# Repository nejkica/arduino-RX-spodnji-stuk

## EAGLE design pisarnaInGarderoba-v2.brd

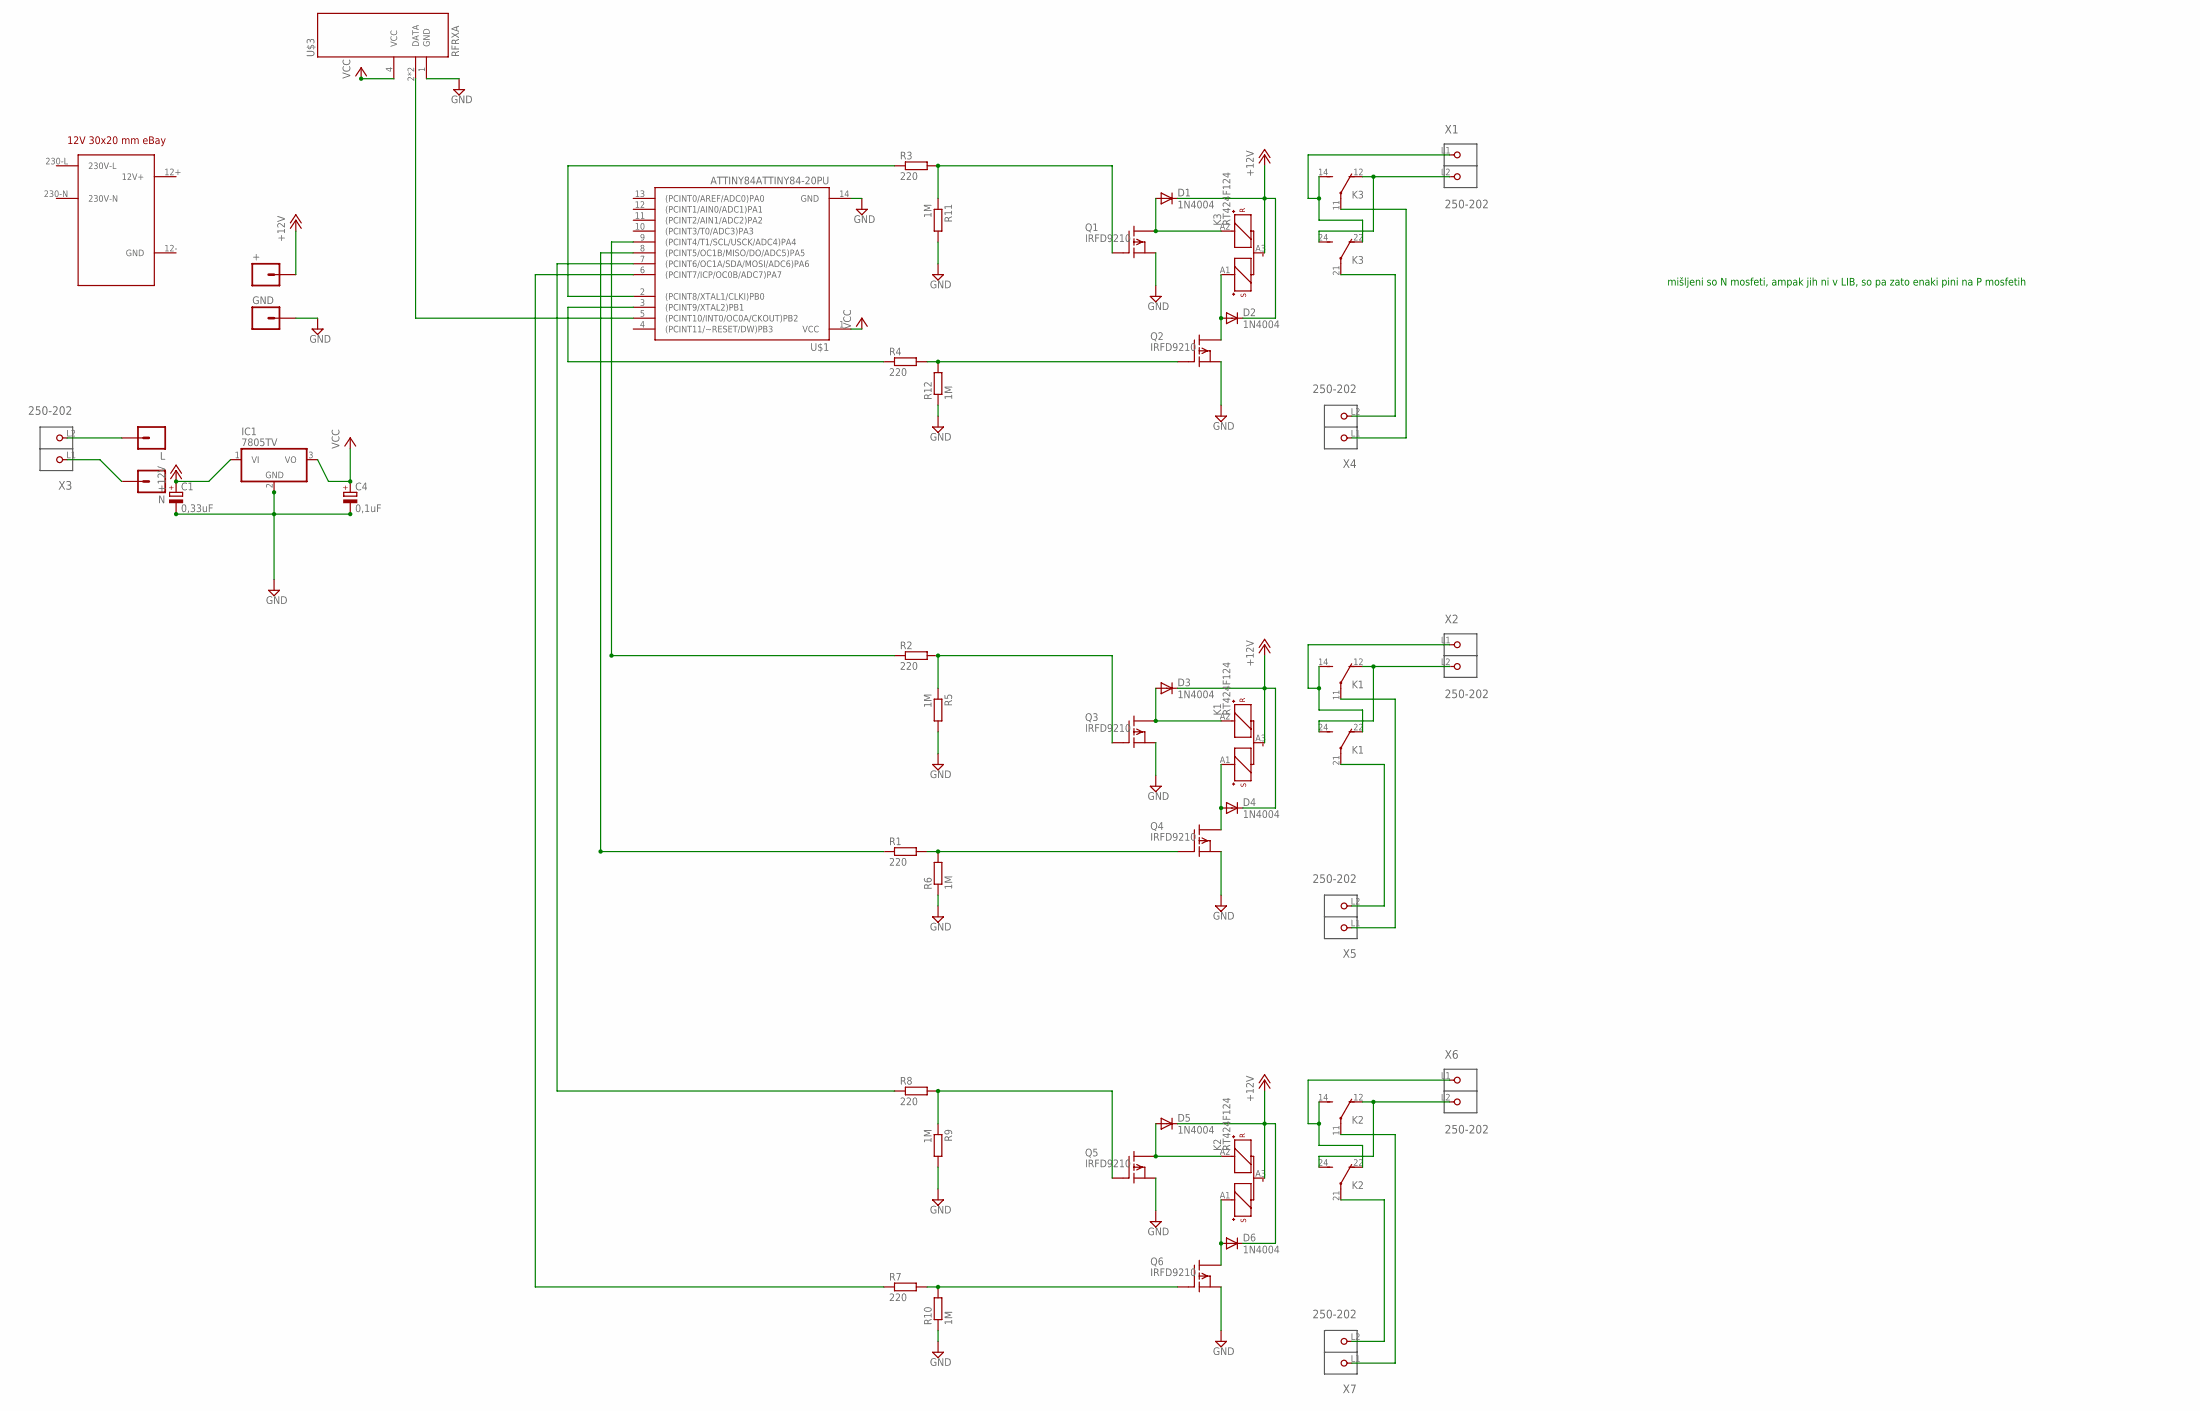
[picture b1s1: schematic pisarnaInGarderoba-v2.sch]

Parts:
+: M01PTH; 1X01
C1: 0,33uF; E2,5-5; MPN SPC15391
C4: 0,1uF; E2,5-5; MPN SPC15391
D1, D2, D3, D4, D5, D6: 1N4004; DO41-10
GND: M01PTH; 1X01
IC1: 7805TV; TO220V
K1, K2, K3: RT424F124; RT424
L: M01PTH; 1X01
N: M01PTH; 1X01
Q1, Q2, Q3, Q4, Q5, Q6: IRFD9210; DIL04
R1, R2, R3, R4, R7, R8: 220; 0204/7
R5, R6, R9, R10, R11, R12: 1M; 0204/7
U$1: ATTINY84ATTINY84-20PU; DIL14
U$2: 12V-30X20; 12V30X20
U$3: RFRXA; IC
X1, X2, X3, X4, X5, X6, X7: 250-202; P-250-202

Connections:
+12V: +.1, C1.+, D1.C, D2.C, D3.C, D4.C, D5.C, D6.C, IC1.1 (VI), K1.A3 (-), K2.A3 (-), K3.A3 (-)
GND: C1.-, C4.-, GND.1, IC1.2 (GND), Q1.2 (S), Q2.2 (S), Q3.2 (S), Q4.2 (S), Q5.2 (S), Q6.2 (S), R5.2, R6.1, R9.2, R10.1, R11.2, R12.1, U$1.14 (GND), U$3.1 (GND)
unnamed: K3.21, X4.L2 (P2)
unnamed: D2.A, K3.A1 (S+), Q2.3 (D), Q2.4 (D)
unnamed: D1.A, K3.A2 (R+), Q1.3 (D), Q1.4 (D)
unnamed: Q2.1 (G), R4.2, R12.2
unnamed: K3.11, X4.L1 (P1)
unnamed: Q1.1 (G), R3.2, R11.1
unnamed: K3.12 (O), K3.24 (S), X1.L2 (P2)
unnamed: K3.14 (S), K3.22 (O), X1.L1 (P1)
unnamed: R3.1, U$1.2 ((PCINT8/XTAL1/CLKI)PB0)
unnamed: R4.1, U$1.3 ((PCINT9/XTAL2)PB1)
unnamed: U$1.5 ((PCINT10/INT0/OC0A/CKOUT)PB2), U$3.2 (DATA), U$3.3 (DATA)
unnamed: K1.21, X5.L2 (P2)
unnamed: K1.11, X5.L1 (P1)
unnamed: Q4.1 (G), R1.2, R6.2
unnamed: Q3.1 (G), R2.2, R5.1
unnamed: R8.1, U$1.7 ((PCINT6/OC1A/SDA/MOSI/ADC6)PA6)
unnamed: D4.A, K1.A1 (S+), Q4.3 (D), Q4.4 (D)
unnamed: R2.1, U$1.9 ((PCINT4/T1/SCL/USCK/ADC4)PA4)
unnamed: R1.1, U$1.8 ((PCINT5/OC1B/MISO/DO/ADC5)PA5)
unnamed: D3.A, K1.A2 (R+), Q3.3 (D), Q3.4 (D)
unnamed: K1.12 (O), K1.24 (S), X2.L2 (P2)
unnamed: K1.14 (S), K1.22 (O), X2.L1 (P1)
unnamed: R7.1, U$1.6 ((PCINT7/ICP/OC0B/ADC7)PA7)
unnamed: Q6.1 (G), R7.2, R10.2
unnamed: Q5.1 (G), R8.2, R9.1
unnamed: D6.A, K2.A1 (S+), Q6.3 (D), Q6.4 (D)
unnamed: D5.A, K2.A2 (R+), Q5.3 (D), Q5.4 (D)
unnamed: K2.12 (O), K2.24 (S), X6.L2 (P2)
unnamed: K2.14 (S), K2.22 (O), X6.L1 (P1)
unnamed: K2.21, X7.L2 (P2)
unnamed: K2.11, X7.L1 (P1)
unnamed: L.1, X3.L2 (P2)
unnamed: N.1, X3.L1 (P1)
VCC: C4.+, IC1.3 (VO), U$1.1 (VCC), U$3.4 (VCC)

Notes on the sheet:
mišljeni so N mosfeti, ampak jih ni v LIB, so pa zato enaki pini na P mosfetih

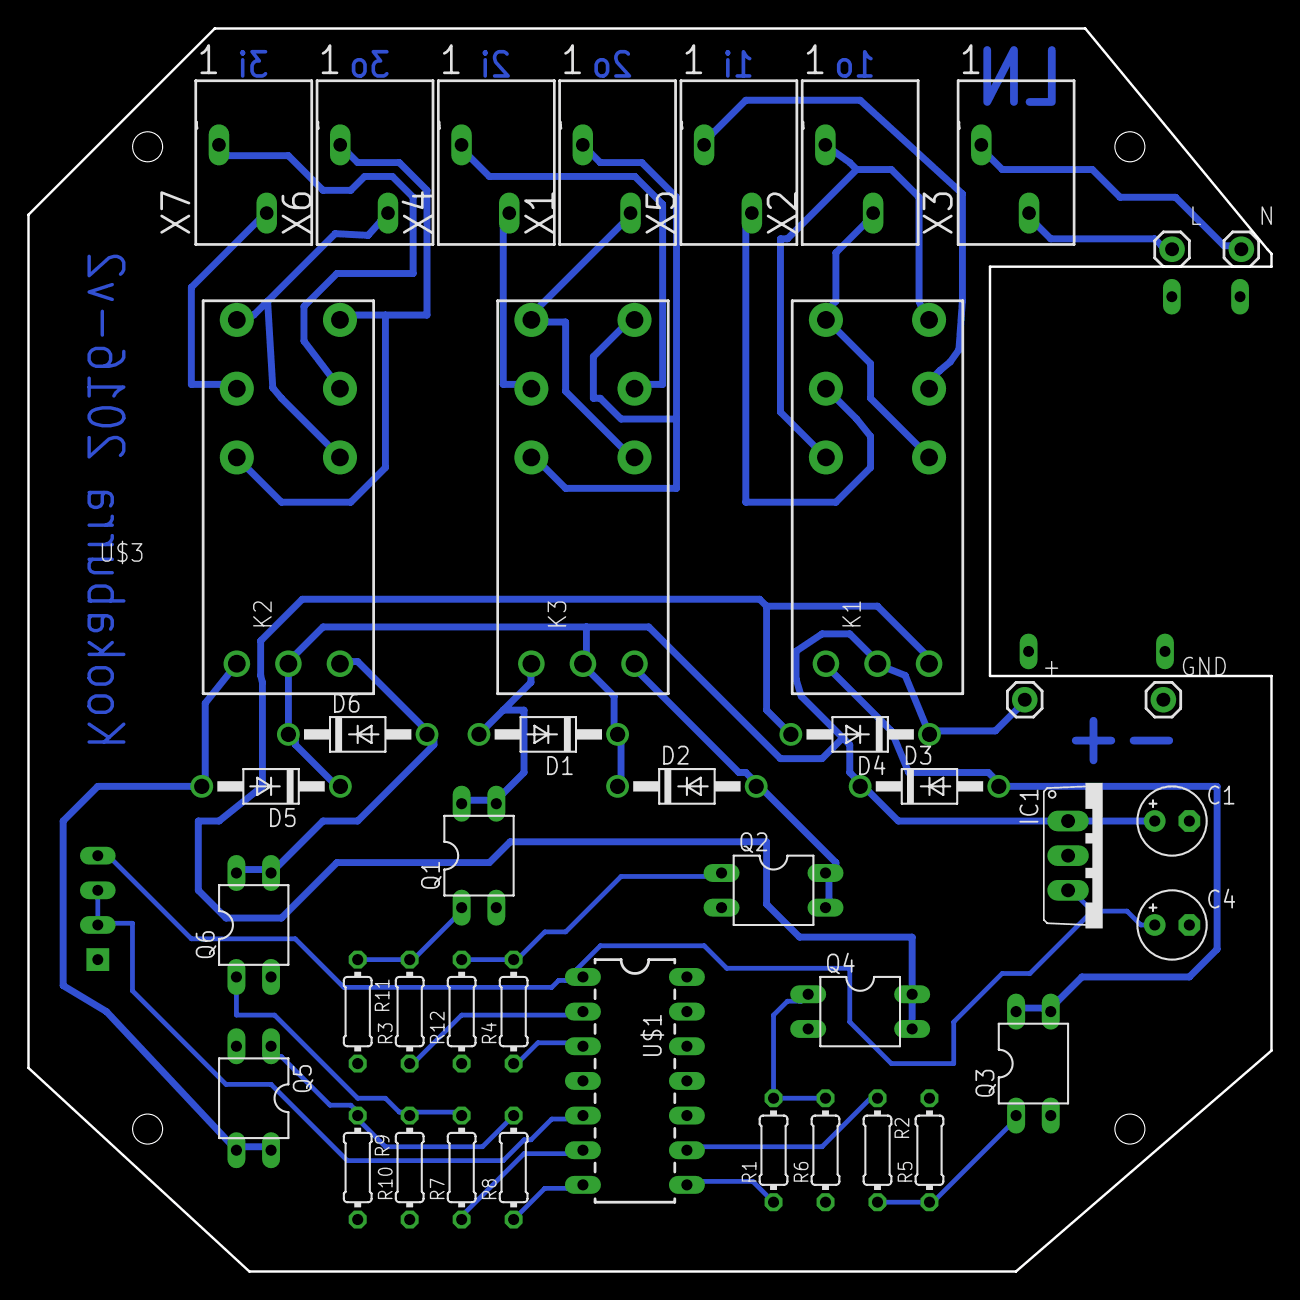
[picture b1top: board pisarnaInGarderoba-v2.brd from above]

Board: 2 copper layers, 91.1 x 91.1 mm, 44 parts (0 on the bottom side), 36 nets.

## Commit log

2017-05-24 upload komplet za spodnji stuk
2017-05-24 dodam še arduino datoteko

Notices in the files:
parts and their libraries:
SparkFun-Connectors: Licensing: Creative Commons ShareAlike 4.0 International - https://creativecommons.org/licenses/by-sa/4.0
